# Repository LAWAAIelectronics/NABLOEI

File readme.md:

# ReadMe #
This repository provides:
- the full KiCad project, including gerbers plotted to the specifications of JLCPCB
- a PDF of the schematic for those who do not use KiCad
- the Arduino code
- a PNG of the user manual like bellow

The gerbers, pdf schematic and firmware are not located under the code tab but can be downloaded in releases.

All of this documentation is free for you to use, all I ask is that no direct copies of this pedal are made for sale.

Thank you.

LAWAAI

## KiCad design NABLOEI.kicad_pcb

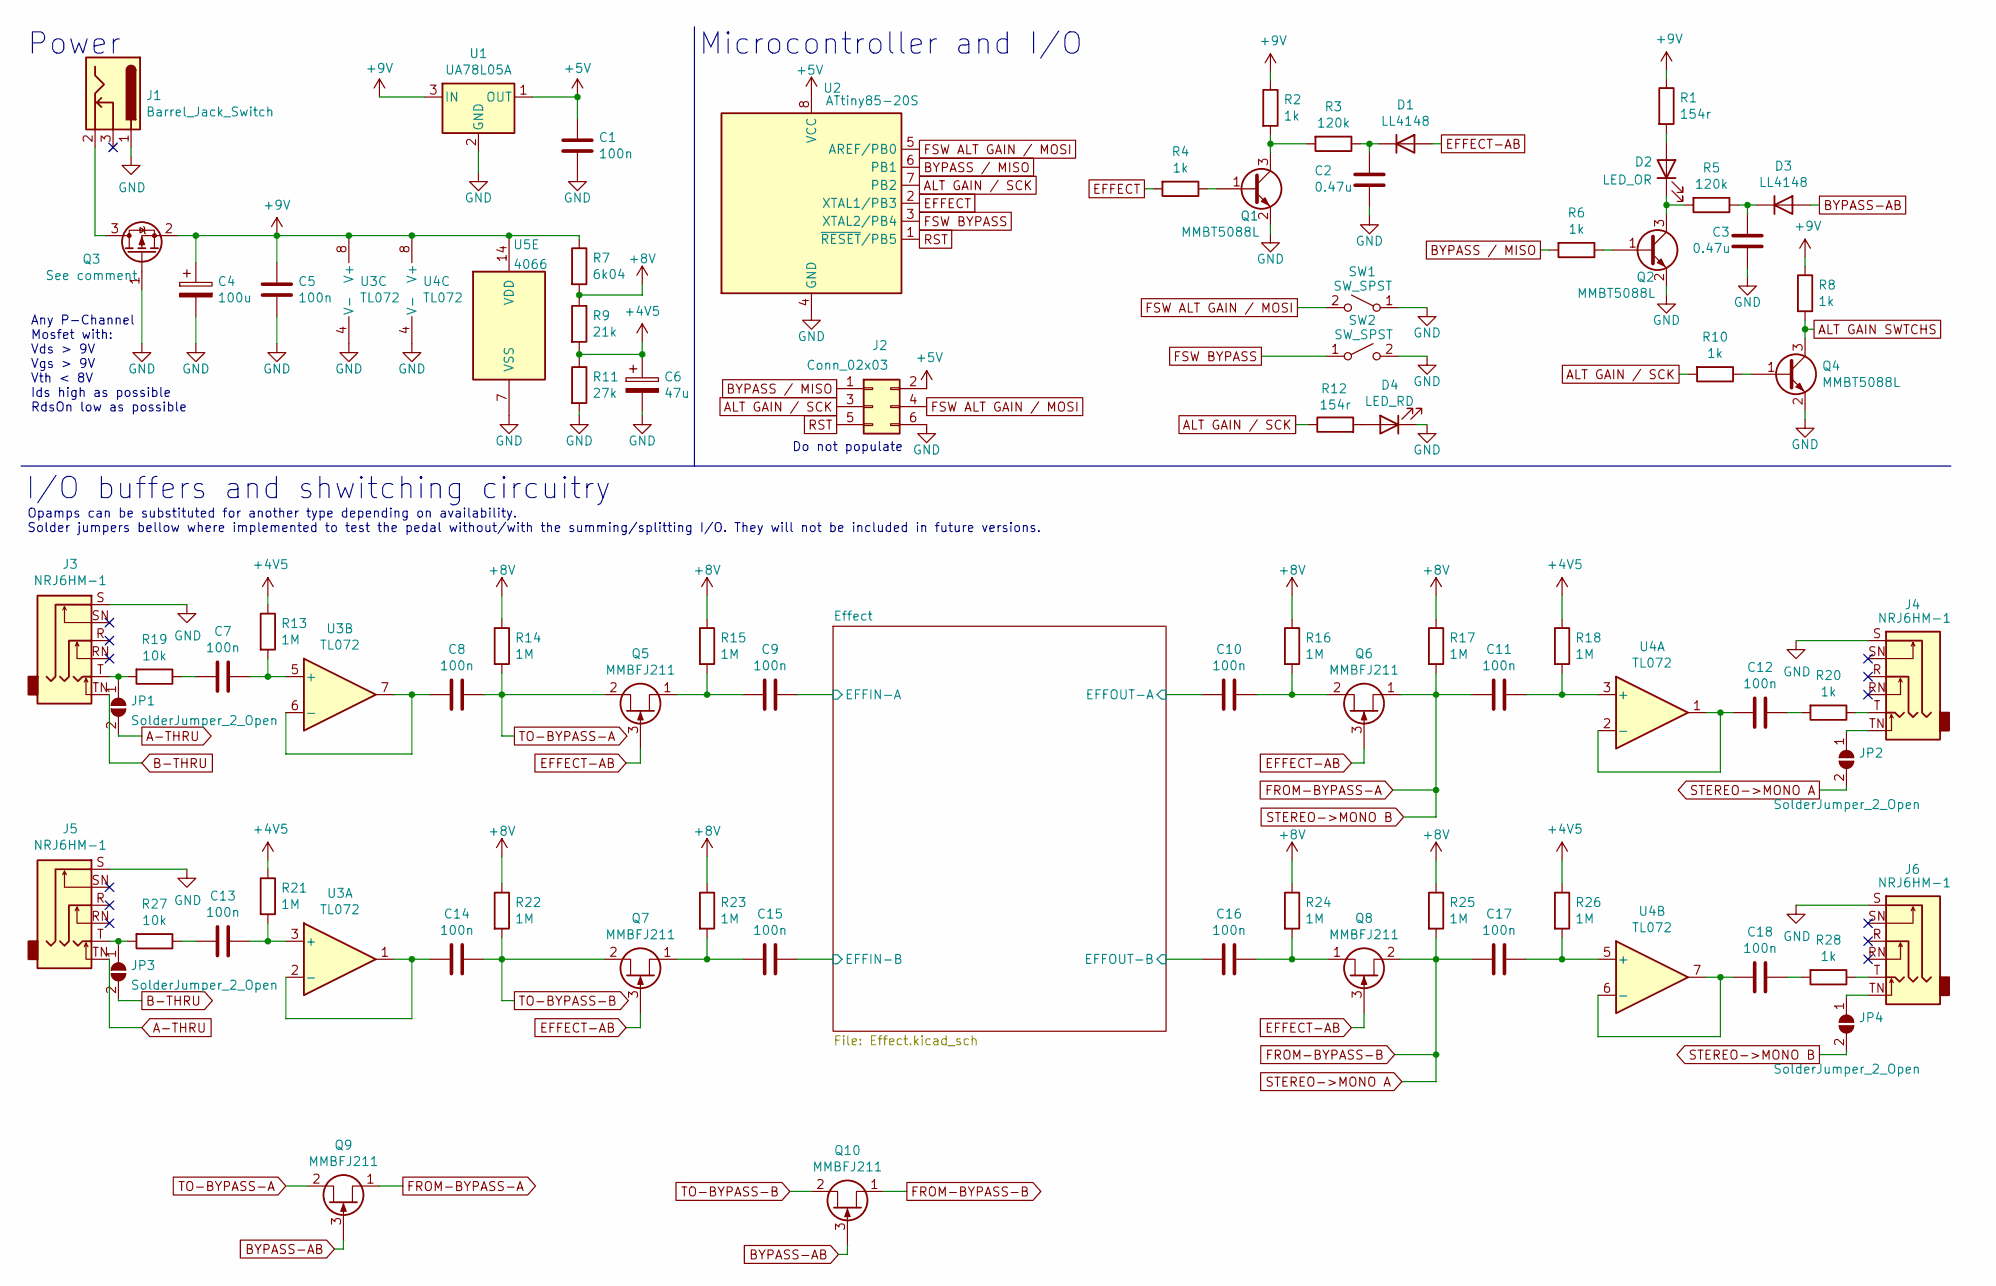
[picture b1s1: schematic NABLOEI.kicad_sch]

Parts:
C1, C5, C7, C8, C9, C10, C11, C12, C13, C14, C15, C16, C17, C18: 100n; C_1206_3216Metric
C2, C3: 0.47u; C_1206_3216Metric
C4: 100u; CP_Elec_8x5.4
C6: 47u; CP_Elec_5x5.4
D1, D3: LL4148; D_MiniMELF
D2: LED_OR; LED_1206_3216Metric
D4: LED_RD; LED_1206_3216Metric
J1: Barrel_Jack_Switch; BarrelJack_Horizontal
J2: Conn_02x03; PinHeader_2x03_P2.54mm_Vertical
J3, J4, J5, J6: NRJ6HM-1; Jack_6.35mm_Neutrik_NRJ6HM-1_Horizontal
JP1, JP2, JP3, JP4: SolderJumper_2_Open; SolderJumper-2_P1.3mm_Open_RoundedPad1.0x1.5mm
Q1, Q2, Q4: MMBT5088L; SOT-23
Q3: See comment; SOT-23
Q5, Q6, Q7, Q8, Q9, Q10: MMBFJ211; SOT-23
R1, R12: 154r; R_1206_3216Metric
R2, R4, R6, R8, R10, R20, R28: 1k; R_1206_3216Metric
R3, R5: 120k; R_1206_3216Metric
R7: 6k04; R_1206_3216Metric
R9: 21k; R_1206_3216Metric
R11: 27k; R_1206_3216Metric
R13, R14, R15, R16, R17, R18, R21, R22, R23, R24, R25, R26: 1M; R_1206_3216Metric
R19, R27: 10k; R_1206_3216Metric
SW1, SW2: SW_SPST; Molex_Micro-Latch_53254-0270_1x02_P2.00mm_Horizontal
U1: UA78L05A; SOT-89-3
U2: ATtiny85-20S; SOIC-8W_5.3x5.3mm_P1.27mm
U3, U4: TL072; SOIC-8W_5.3x5.3mm_P1.27mm
U5: 4066; SOIC-14_3.9x8.7mm_P1.27mm

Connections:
+4V5: C6.1, R9.2, R11.1, R13.1, R18.1, R21.1, R26.1
+5V: C1.1, J2.2, U1.1 (OUT), U2.8 (VCC)
+8V: R7.2, R9.1, R14.1, R15.1, R16.1, R17.1, R22.1, R23.1, R24.1, R25.1
+9V: C4.1, C5.1, Q3.2 (S), R1.1, R2.1, R7.1, R8.1, U1.3 (IN), U3.8 (V+), U4.8 (V+), U5.14 (VDD); also elsewhere on the board
/Effect/EFFIN-A: C9.1; also elsewhere on the board
/Effect/EFFIN-B: C15.1; also elsewhere on the board
/Effect/EFFOUT-A: C10.2; also elsewhere on the board
/Effect/EFFOUT-B: C16.2; also elsewhere on the board
A-THRU: J5.TN, JP1.2 (B)
ALT GAIN SWTCHS: Q4.3 (C), R8.2; also elsewhere on the board
ALT GAIN / SCK: J2.3, R10.2, R12.1, U2.7 (PB2)
B-THRU: J3.TN, JP3.2 (B)
BYPASS / MISO: J2.1, R6.2, U2.6 (PB1)
BYPASS-AB: D3.2 (A), Q9.3 (G), Q10.3 (G)
EFFECT: R4.2, U2.2 (XTAL1/PB3)
EFFECT-AB: D1.2 (A), Q5.3 (G), Q6.3 (G), Q7.3 (G), Q8.3 (G)
FROM-BYPASS-A: C11.2, JP4.2 (B), Q6.1 (S), Q9.1 (S), R17.2
FROM-BYPASS-B: C17.2, JP2.2 (B), Q8.2 (D), Q10.1 (S), R25.2
FSW ALT GAIN / MOSI: J2.4, SW1.2 (B), U2.5 (AREF/PB0)
FSW BYPASS: SW2.1 (A), U2.3 (XTAL2/PB4)
GND: C1.2, C2.2, C3.2, C4.2, C5.2, C6.2, D4.1 (K), J1.1, J2.6, J3.S, J4.S, J5.S, J6.S, Q1.2 (E), Q2.2 (E), Q3.1 (G), Q4.2 (E), R11.2, SW1.1 (A), SW2.2 (B), U1.2 (GND), U2.4 (GND), U3.4 (V-), U4.4 (V-), U5.7 (VSS); also elsewhere on the board
unnamed: C2.1, D1.1 (K), R3.1
unnamed: C3.1, D3.1 (K), R5.1
unnamed: C7.1, R13.2, U3.5 (+)
unnamed: C7.2, R19.1
unnamed: C8.2, U3.6 (-), U3.7
unnamed: C9.2, Q5.1 (S), R15.2
unnamed: C10.1, Q6.2 (D), R16.2
unnamed: C11.1, R18.2, U4.3 (+)
unnamed: C12.1, R20.2
unnamed: C12.2, U4.1, U4.2 (-)
unnamed: C13.1, R21.2, U3.3 (+)
unnamed: C13.2, R27.1
unnamed: C14.2, U3.1, U3.2 (-)
unnamed: C15.2, Q7.1 (S), R23.2
unnamed: C16.1, Q8.1 (S), R24.2
unnamed: C17.1, R26.2, U4.5 (+)
unnamed: C18.1, R28.2
unnamed: C18.2, U4.6 (-), U4.7
unnamed: D2.1 (K), Q2.3 (C), R5.2
unnamed: D2.2 (A), R1.2
unnamed: D4.2 (A), R12.2
unnamed: J1.2, Q3.3 (D)
unnamed: J3.T, JP1.1 (A), R19.2
unnamed: J4.T, R20.1
unnamed: J4.TN, JP2.1 (A)
unnamed: J5.T, JP3.1 (A), R27.2
unnamed: J6.T, R28.1
unnamed: J6.TN, JP4.1 (A)
unnamed: Q1.1 (B), R4.1
unnamed: Q1.3 (C), R2.2, R3.2
unnamed: Q2.1 (B), R6.1
unnamed: Q4.1 (B), R10.1
RST: J2.5, U2.1 (~RESET/PB5)
TO-BYPASS-A: C8.1, Q5.2 (D), Q9.2 (D), R14.2
TO-BYPASS-B: C14.1, Q7.2 (D), Q10.2 (D), R22.2

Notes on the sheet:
Microcontroller and I/O
Any P-Channel Mosfet with: Vds > 9V Vgs > 9V Vth < 8V Ids high as possible RdsOn low as possible
Do not populate
Opamps can be substituted for another type depending on availability. Solder jumpers bellow where implemented to test the pedal without/with the summing/splitting I/O. They will not be included in future versions.
I/O buffers and shwitching circuitry
Power

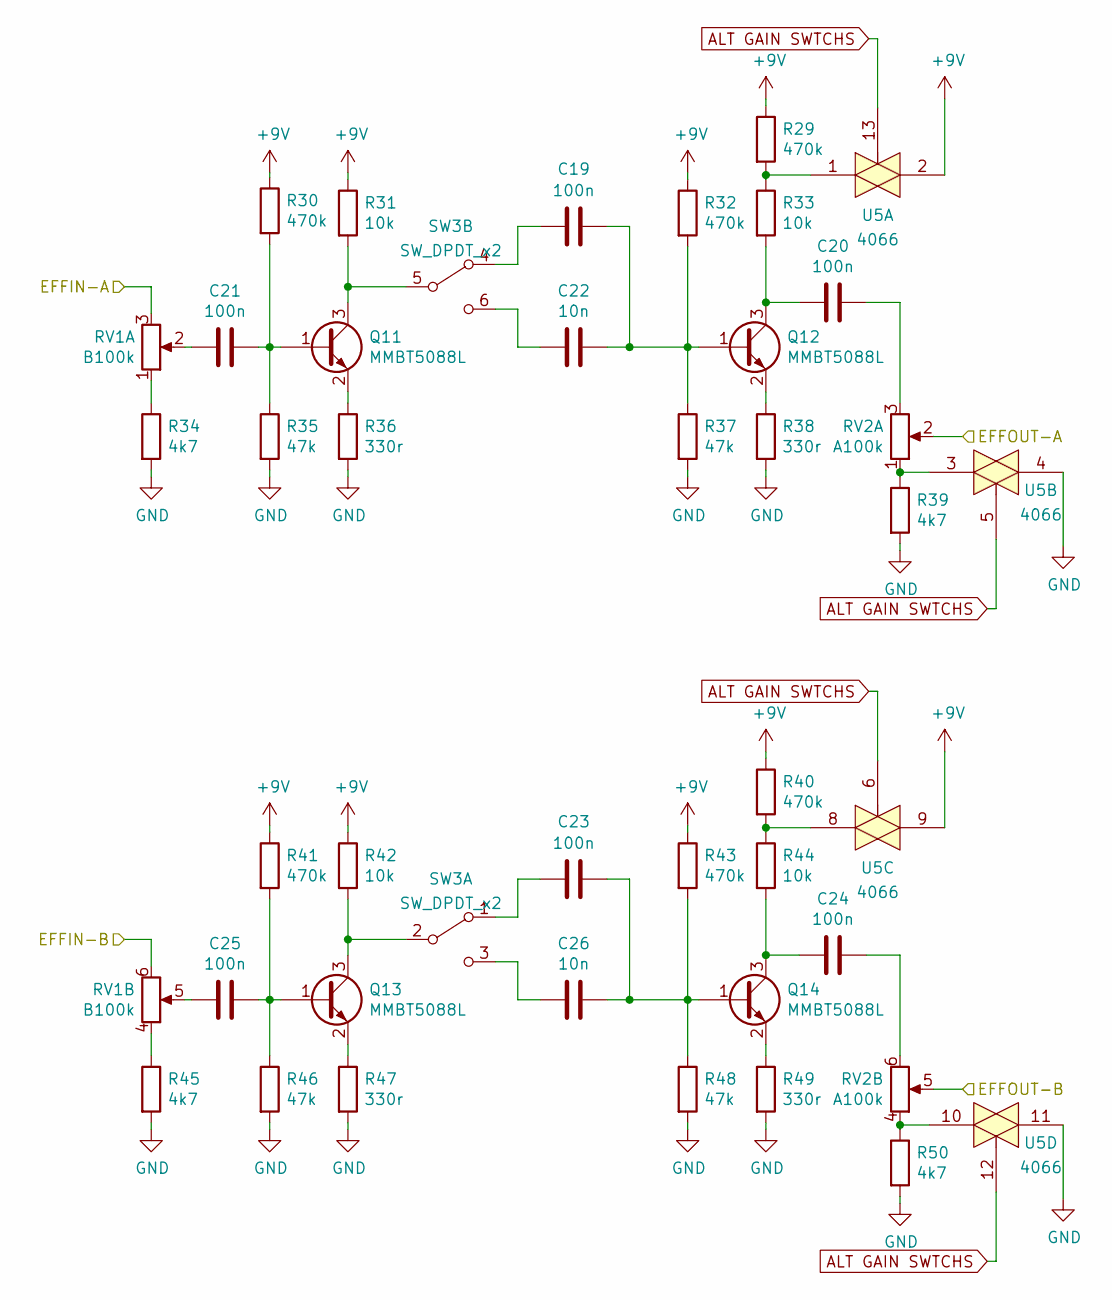
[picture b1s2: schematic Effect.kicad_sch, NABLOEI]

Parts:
C19, C20, C21, C23, C24, C25: 100n; C_1206_3216Metric
C22, C26: 10n; C_1206_3216Metric
Q11, Q12, Q13, Q14: MMBT5088L; SOT-23
R29, R30, R32, R40, R41, R43: 470k; R_1206_3216Metric
R31, R33, R42, R44: 10k; R_1206_3216Metric
R34, R39, R45, R50: 4k7; R_1206_3216Metric
R35, R37, R46, R48: 47k; R_1206_3216Metric
R36, R38, R47, R49: 330r; R_1206_3216Metric
RV1: B100k; Potentiometer_Alpha_RV16A01F-41-15R1_Dual_Vertical
RV2: A100k; Potentiometer_Alpha_RV16A01F-41-15R1_Dual_Vertical
SW3: SW_DPDT_x2; Switch_Dailywell_Electronics_1MD1T1B1M1QES_DPDT_ON-ON
U5: 4066; SOIC-14_3.9x8.7mm_P1.27mm

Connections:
+9V: R29.1, R30.1, R31.1, R32.1, R40.1, R41.1, R42.1, R43.1, U5.2, U5.9; also elsewhere on the board
/Effect/EFFIN-A: RV1.3; also elsewhere on the board
/Effect/EFFIN-B: RV1.6; also elsewhere on the board
/Effect/EFFOUT-A: RV2.2; also elsewhere on the board
/Effect/EFFOUT-B: RV2.5; also elsewhere on the board
ALT GAIN SWTCHS: U5.5, U5.6, U5.12, U5.13; also elsewhere on the board
GND: R34.2, R35.2, R36.2, R37.2, R38.2, R39.2, R45.2, R46.2, R47.2, R48.2, R49.2, R50.2, U5.4, U5.11; also elsewhere on the board
unnamed: C19.1, C22.1, Q12.1 (B), R32.2, R37.1
unnamed: C19.2, SW3.4 (A)
unnamed: C20.1, RV2.3
unnamed: C20.2, Q12.3 (C), R33.2
unnamed: C21.1, Q11.1 (B), R30.2, R35.1
unnamed: C21.2, RV1.2
unnamed: C22.2, SW3.6 (C)
unnamed: C23.1, C26.1, Q14.1 (B), R43.2, R48.1
unnamed: C23.2, SW3.1 (A)
unnamed: C24.1, RV2.6
unnamed: C24.2, Q14.3 (C), R44.2
unnamed: C25.1, Q13.1 (B), R41.2, R46.1
unnamed: C25.2, RV1.5
unnamed: C26.2, SW3.3 (C)
unnamed: Q11.2 (E), R36.1
unnamed: Q11.3 (C), R31.2, SW3.5 (B)
unnamed: Q12.2 (E), R38.1
unnamed: Q13.2 (E), R47.1
unnamed: Q13.3 (C), R42.2, SW3.2 (B)
unnamed: Q14.2 (E), R49.1
unnamed: R29.2, R33.1, U5.1
unnamed: R34.1, RV1.1
unnamed: R39.1, RV2.1, U5.3
unnamed: R40.2, R44.1, U5.8
unnamed: R45.1, RV1.4
unnamed: R50.1, RV2.4, U5.10

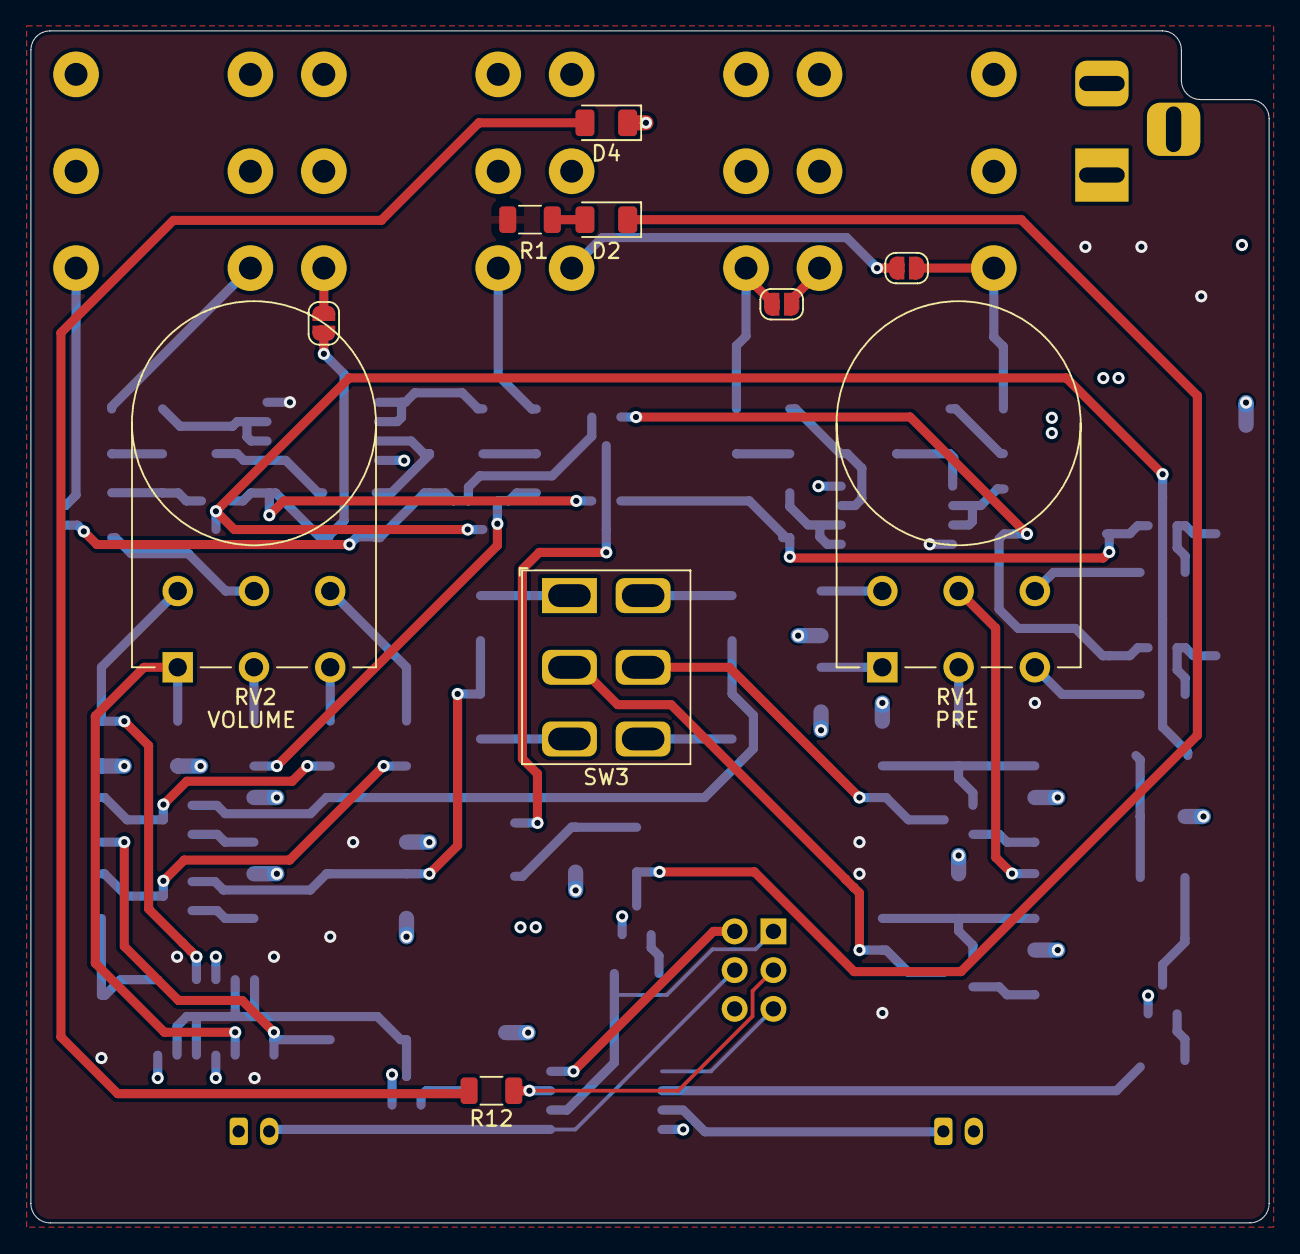
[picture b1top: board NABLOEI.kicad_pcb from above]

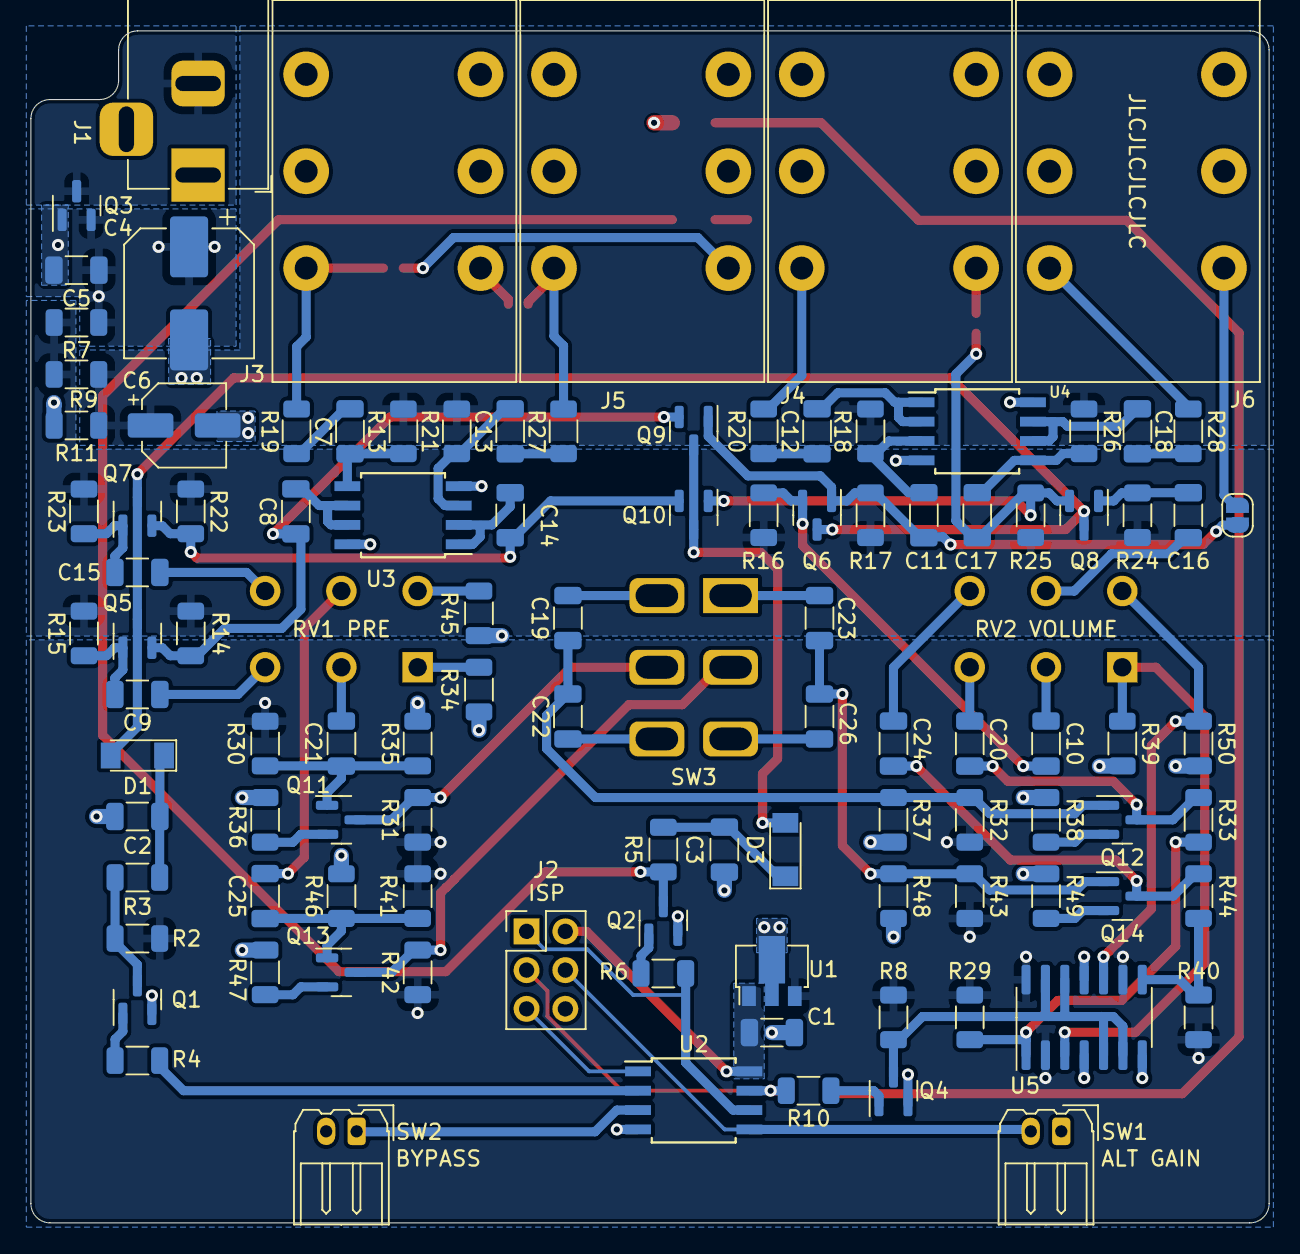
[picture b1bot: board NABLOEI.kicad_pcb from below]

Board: 4 copper layers, 81.2 x 78.1 mm, 114 parts (104 on the bottom side), 82 nets.
